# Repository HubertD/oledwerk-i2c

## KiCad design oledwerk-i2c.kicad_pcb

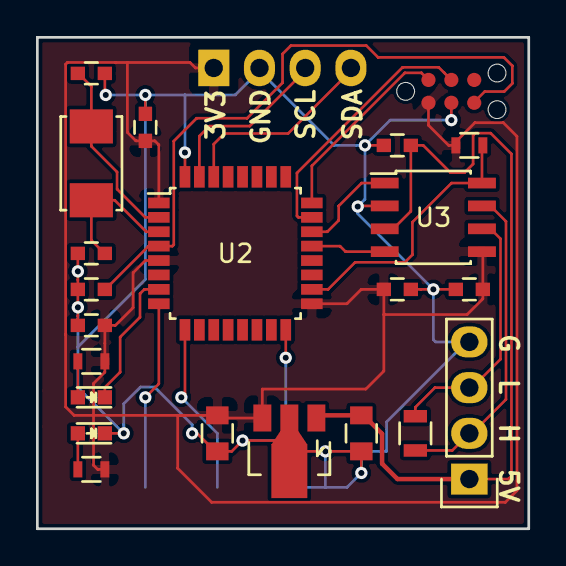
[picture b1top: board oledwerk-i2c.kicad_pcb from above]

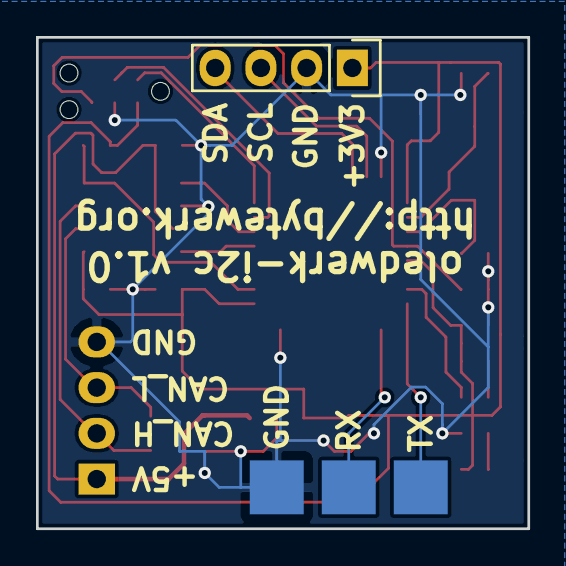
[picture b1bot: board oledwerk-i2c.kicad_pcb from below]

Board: 2 copper layers, 27.3 x 27.3 mm, 26 parts (4 on the bottom side), 20 nets.

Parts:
C1, C2: 10uF; C_0805
C3, C4, C7, C8, C9, C10: 100nF; C_0603
C5, C6: 18pF; C_0603
D1: green; LED_0603
D2: red; LED_0603
P1, P2: CONN_01X04; Pin_Header_Straight_1x04
R1, R2: 1K; R_0603
R3: 10K; R_0603
R4: dnp; R_0805
U1: MCP1754ST-3302E/MB; SOT89-3_Housing
U2: STM32F042K6Tx; LQFP-32_7x7mm_Pitch0.8mm
U3: TJA1051T/3; SOIC-8_3.9x4.9mm_Pitch1.27mm
W1: TX; Measurement_Point_Square-SMD-Pad_Big
W2: RX; Measurement_Point_Square-SMD-Pad_Big
W3: GND; Measurement_Point_Square-SMD-Pad_Big
X1: CON_SWD; TC2030-NL
Y1: 8MHz; ABM3

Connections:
+3V3: C2.1, C3.1, C8.1, C9.1, C10.1, P1.1, R1.1, R2.1, R3.1, U1.3, U2.1, U2.5, U2.17, U3.5, X1.1
+5V: C1.1, C4.1, P2.1, U1.1, U3.3
CAN_H: P2.2, R4.1, U3.7
CAN_L: P2.3, R4.2, U3.6
CAN_RXD: U2.21, U3.4
CAN_S: R3.2, U2.18, U3.8
CAN_TXD: U2.22, U3.1
GND: C1.2, C2.2, C3.2, C4.2, C5.2, C6.2, C7.2, C8.2, C9.2, C10.2, D1.1, P1.2, P2.4, U1.2, U2.16, U2.32, U3.2, W3.1, X1.3
NRST: C7.1, U2.4, X1.5
unnamed: C5.1, U2.2, Y1.1
unnamed: C6.1, U2.3, Y1.2
unnamed: D1.2, R1.2
unnamed: D2.2, R2.2
SCL: P1.3, U2.31
SDA: P1.4, U2.30
SWCLK: U2.24, X1.2
SWDIO: U2.23, X1.4
USART_RX: U2.9, W2.1
USART_TX: U2.8, W1.1
USR_LED: D2.1, U2.7

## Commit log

2016-06-26 initial checkin
